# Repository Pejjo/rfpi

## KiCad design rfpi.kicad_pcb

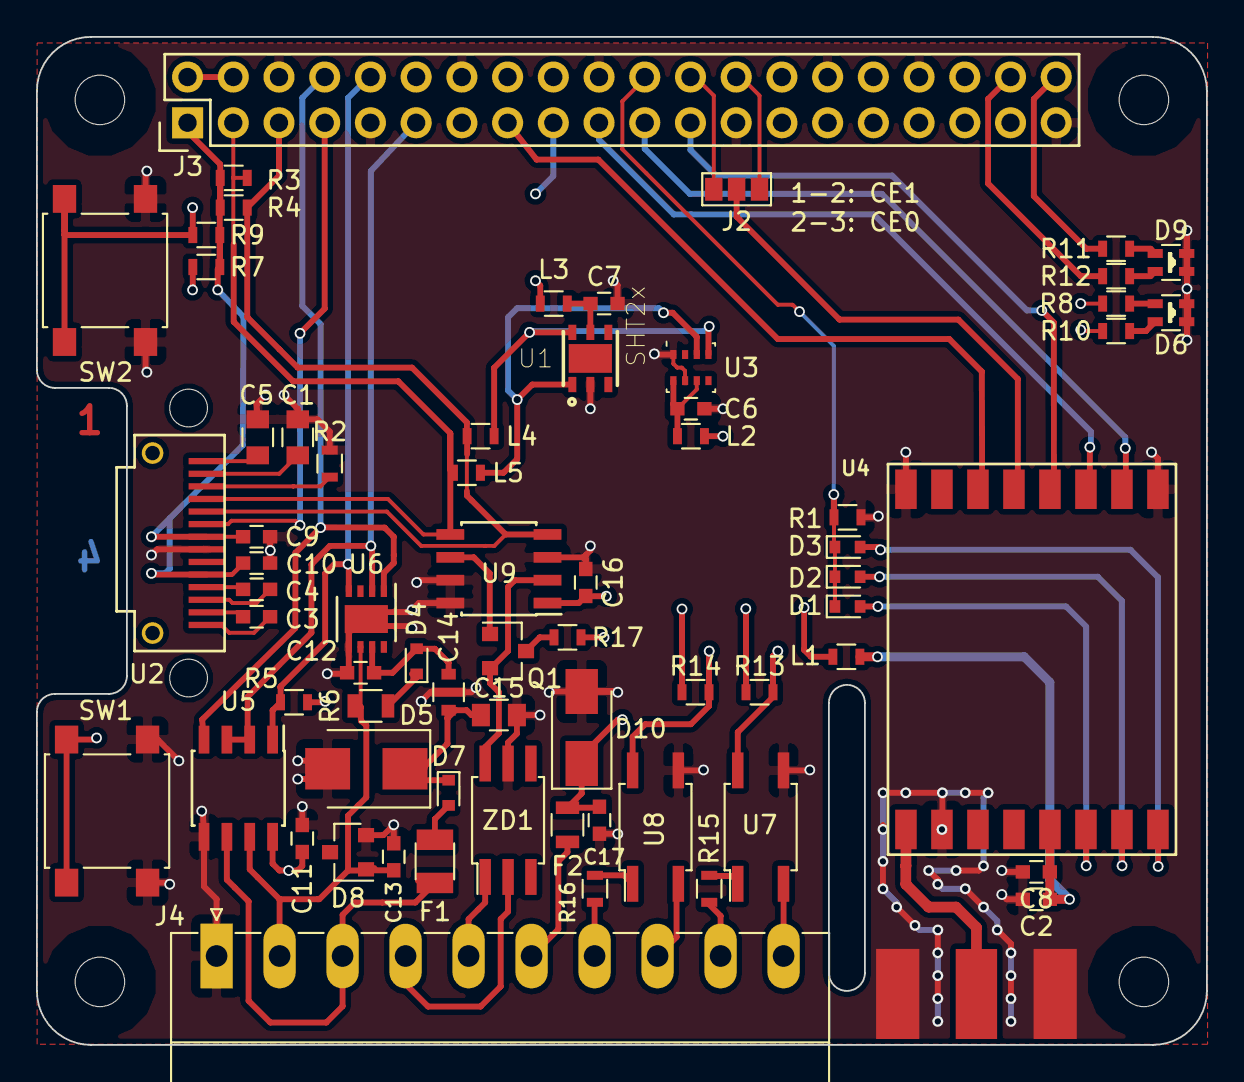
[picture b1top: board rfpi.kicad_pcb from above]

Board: 4 copper layers, 65.0 x 56.0 mm, 68 parts (0 on the bottom side), 63 nets.

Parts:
C1, C5, C15: 2u2; C_0805
C2: 10u; C_0603
C3, C4, C8, C9, C10: 1u; C_0603
C6, C13: C_Small; C_0603
C7, C11, C12, C16, C17: 100n; C_0603
C14: 1000p 50V .4A; C_0805_3
D1, D2, D3, D4: 1N4148WT; D_SOD-523
D5: SMBJ28A; D_SMB
D6, D9: LED_Dual_ACAC; Dual_Led_0605
D7: 1N4848WT; D_SOD-523
D8: NUP1105LT1G; SOT-23
D10: SMLVT3V3; D_SMA
F1: 125mA; Fuse_SMD1206_Reflow
F2: 0805L010YR; R_0805
J1: CONN_COAXIAL; SMA-EDGE
J2: GS3
J3: Raspberry_Pi_2_3; Pin_Header_Straight_2x20
J4: Screw_Terminal_1x10; PhoenixContact_MC-G_10x3.50mm_Angled
L1, L2, L4, L5: BLM11A102S; L_0603
L3: 600Ohm; L_0603
Q1: n.p; SOT-23
R1, R3, R4, R5, R7, R9, R13, R14: 3k3; R_0603
R2: 400k; R_0603
R6: 1k; L_0805
R8, R10, R11, R12, R15, R16: 1k; R_0603
R17: n.p; R_0603
SW1, SW2: SW_Push; SW_SPST_B3S-1000
U1: SHT2x; SON100P300X300X110-7N
U2: OLED14; MiasOled14
U3: NPA-201; HCLGA-8_2x2.5mm_Pitch0.65mm_ClockwisePinNumbering
U4: RFM95HW; RFM69HW_SMD
U5: MAX3072E; SOIC-8_3.9x4.9mm_Pitch1.27mm
U6: TJA1029TK; DFN-8-1EP_3x3mm_Pitch0.65mm
U7, U8: PC817; SO-4_4.4x3.6mm_Pitch2.54mm
U9: DS2482-100; SOIC-8_3.9x4.9mm_Pitch1.27mm
ZD1: DS9503P; SO-6_4.4x3.6mm_Pitch1.27mm

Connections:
+3V3: C9.1, C10.1, C11.1, C16.1, C17.1, D10.1, F2.1, J3.1, J3.17, L1.1, L2.1, L3.1, R3.1, R4.1, R5.1, R7.1, R9.1, R13.1, R14.1, R17.1, U2.5, U2.8, U5.8, U9.1
+5V: J3.2, J3.4
GND: C1.2, C2.2, C5.2, C6.2, C7.2, C8.2, C9.2, C10.2, C11.2, C12.2, C13.2, C14.2, C15.2, C16.2, C17.2, D5.2, D6.2, D6.4, D8.2, D9.2, D9.4, D10.2, J1.2, J3.6, J3.9, J3.14, J3.20, J3.25, J3.30, J3.34, J3.39, J4.1, R1.2, R2.2, SW1.2, SW2.2, U1.2, U2.7, U3.1, U3.7, U4.1, U4.8, U4.10, U5.5, U6.5, U6.9, U7.3, U8.3, U9.3, U9.7, U9.8, ZD1.5
unnamed: C1.1, U2.13
unnamed: C2.1, C8.1, L1.2, U4.13
unnamed: C3.1, U2.1
unnamed: C3.2, U2.2
unnamed: C4.1, U2.3
unnamed: C4.2, U2.4
unnamed: C5.1, U2.14
unnamed: C6.1, L2.2, U3.6, U3.8
unnamed: C7.1, L3.2, U1.5
unnamed: C12.1, C14.1, D4.2, U6.7
unnamed: C13.1, D8.1, J4.2, R6.2, U5.7, U6.6
unnamed: C14.3, C15.1, D5.1, D7.1
unnamed: D1.2, U4.14
unnamed: D2.2, U4.15
unnamed: D3.2, U4.16
unnamed: D4.1, R6.1
unnamed: D6.1, R10.2
unnamed: D6.3, R8.1
unnamed: D7.2, F1.2
unnamed: D9.1, R12.1
unnamed: D9.3, R11.2
unnamed: F1.1, J4.3, U5.6
unnamed: J1.1, U4.9
unnamed: J2.1, J3.26
unnamed: J2.2, U4.5
unnamed: J2.3, J3.24
unnamed: J3.3, L5.1, R3.2, U2.11, U9.5
unnamed: J3.5, L4.1, R4.2, U2.10, U9.4
unnamed: J3.7, U2.9
unnamed: J3.8, U5.4, U6.1
unnamed: J3.10, R5.2, U5.1, U6.4
unnamed: J3.11, U5.2, U5.3, U6.2
unnamed: J3.12, R9.2, SW2.1
unnamed: J3.13, R7.2, SW1.1
unnamed: J3.16, R10.1
unnamed: J3.18, R8.2
unnamed: J3.19, U4.3
unnamed: J3.21, U4.2
unnamed: J3.23, U4.4
unnamed: J3.36, R14.2, U8.4
unnamed: J3.37, R13.2, U7.4
unnamed: J3.38, R12.2
unnamed: J3.40, R11.1
unnamed: J4.7, R16.1
unnamed: J4.8, U8.2
unnamed: J4.9, R15.1
unnamed: J4.10, U7.2
unnamed: L4.2, U1.6, U3.4
unnamed: L5.2, U1.1, U3.3
unnamed: Q1.1, U9.6
unnamed: Q1.2, U9.2, ZD1.6
unnamed: Q1.3, R17.2
unnamed: R2.1, U2.12
unnamed: R15.2, U7.1
unnamed: R16.2, U8.1
OW+: F2.2, J4.6
OW-: J4.4, ZD1.2
OWD: J4.5, ZD1.1
RF_Int: D1.1, D2.1, D3.1, J3.22, R1.1
RF_Rst: J3.15, U4.6
